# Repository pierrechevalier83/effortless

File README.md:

# WIP

This is not ready for any kind of public consumption.
It's just on GitHub as a backup for now.

It's the design of my next keyboard that is a work-in-progress.

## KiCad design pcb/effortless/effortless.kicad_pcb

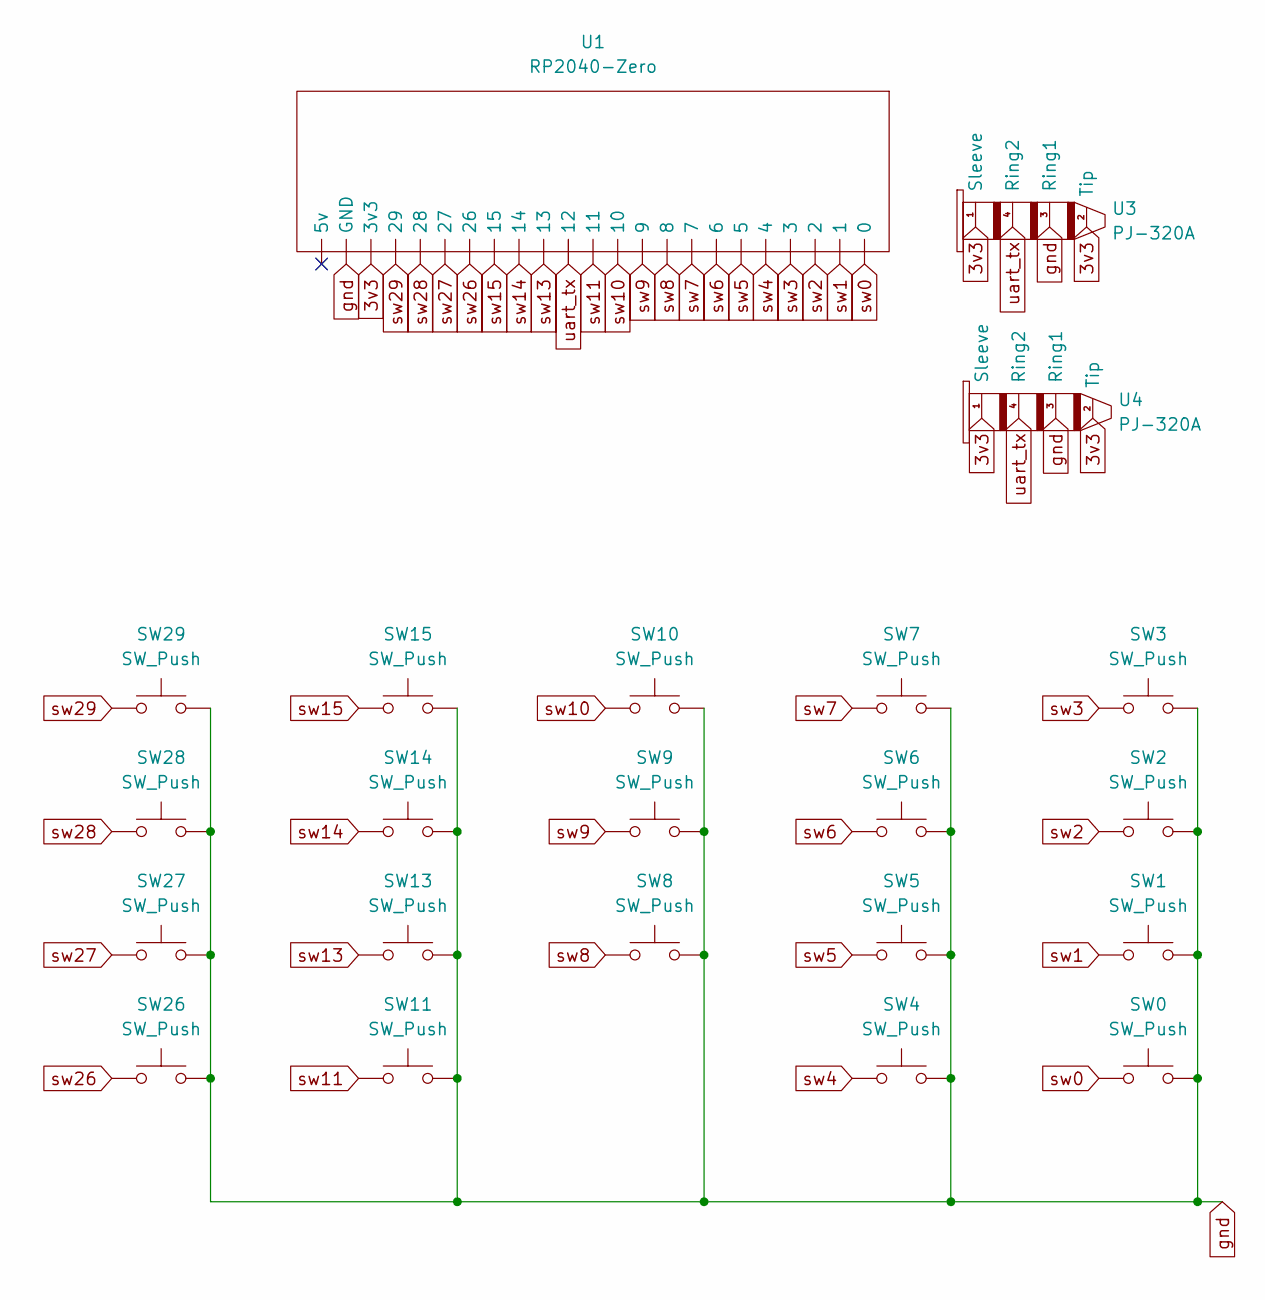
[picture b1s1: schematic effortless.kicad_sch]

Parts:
SW0, SW1, SW2, SW3, SW4, SW5, SW6, SW7, SW8, SW9, SW10, SW11, SW13, SW14, SW15, SW26, SW27, SW28, SW29: SW_Push; effortless_switch
U1: RP2040-Zero
U3, U4: PJ-320A

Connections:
3v3: U1.3v3, U3.1 (Sleeve), U3.2 (Tip), U4.1 (Sleeve), U4.2 (Tip)
gnd: SW0.2, SW1.2, SW2.2, SW3.2, SW4.2, SW5.2, SW6.2, SW7.2, SW8.2, SW9.2, SW10.2, SW11.2, SW13.2, SW14.2, SW15.2, SW26.2, SW27.2, SW28.2, SW29.2, U1.GND, U3.3 (Ring1), U4.3 (Ring1)
sw0: SW0.1, U1.0
sw1: SW1.1, U1.1
sw2: SW2.1, U1.2
sw3: SW3.1, U1.3
sw4: SW4.1, U1.4
sw5: SW5.1, U1.5
sw6: SW6.1, U1.6
sw7: SW7.1, U1.7
sw8: SW8.1, U1.8
sw9: SW9.1, U1.9
sw10: SW10.1, U1.10
sw11: SW11.1, U1.11
sw13: SW13.1, U1.13
sw14: SW14.1, U1.14
sw15: SW15.1, U1.15
sw26: SW26.1, U1.26
sw27: SW27.1, U1.27
sw28: SW28.1, U1.28
sw29: SW29.1, U1.29
uart_tx: U1.12, U3.4 (Ring2), U4.4 (Ring2)

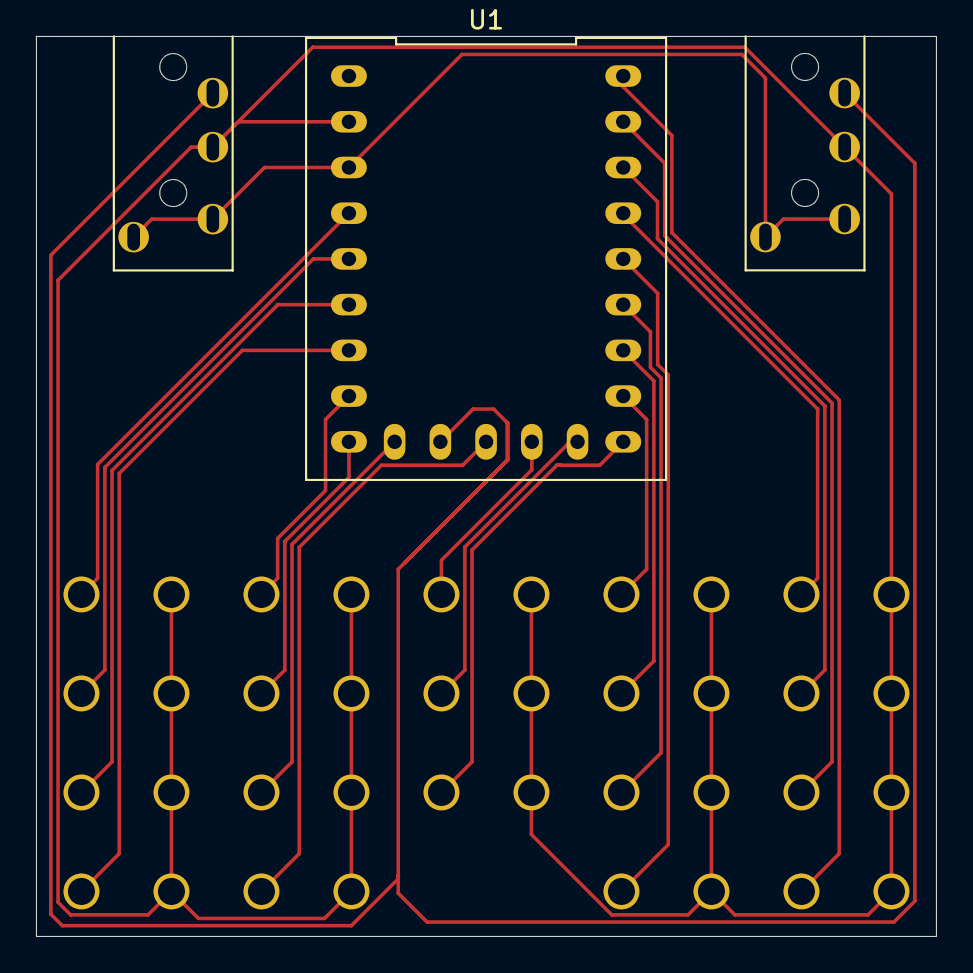
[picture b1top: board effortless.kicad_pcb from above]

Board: 2 copper layers, 50.0 x 50.0 mm, 22 parts (0 on the bottom side), 22 nets.

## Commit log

2024-12-01 Add opencascade-rs as a submodule
2024-12-01 Add gitignore
2024-12-01 Start writing the 3d model for the keyboard
    Early days.
    For now, we have
    * defined the geometry of a single switch
    * defined the geometry of the main switch matrix
    There are a number of TODOs:
    * hard-coded numbers as I'm tinkering
2024-12-01 Add a readme reflecting the current status of this project
2024-12-01 Add submodules for PCB
2024-12-01 Ignore PCB outputs
2024-12-02 Add PCB
2024-12-02 Remove scratchpad.rs
2024-12-05 Fix incorrect y spacing
2024-12-05 Rought sketch a pair of thumbs. It's not attached to the keyboard yet
2024-12-05 Add thumbs that do nothing yet. Simplify ProjectedXYSketch
2024-12-05 Clean-up right face, rigourously define y lofts
2024-12-05 Rename sketches consistently
2024-12-05 Rigorously define the x spacing
    Only cut if the column is above another to avoid weird artifact.
    Code is hacky for now, but principle is sound.
2024-12-05 Use margin in every direction to reduce the number of sketches necessary
2024-12-05 Unify the thumbs to the main body
    It now needs a couple extra cuts above the thumbs, but that allows for
    a flowing shape all around the body of the keyboard
2024-12-05 Refine the shape just a touch
2024-12-05 Streamline the shape some more
2024-12-05 Define cutout above the thumbs
2024-12-05 Make the thumbs cutout a bit prettyer
2024-12-06 Fix stickyness on column 2
2024-12-18 Cut-out the main pcb
2024-12-18 Cut-out the rp2040, offset electronics by 3mm
2024-12-18 Ignore lock files
2024-12-18 Cut-out the jack
2024-12-18 Give margin for PCB and jack so it can slide in at an angle
2024-12-21 Add cutouts to access jack and USB C
2024-12-21 Brute force the switch wire holes with straight lines
    It doesn't look good as bare wires would short each other, but it's a
    start.
    We'll need to think of nicer routing next.
2024-12-21 Hard-code a routing that just about works
    It's hairy and manually tuned, but it avoids wires intersecting each
    other and it connects every switch on the plate to their PCB holes.
2024-12-21 Wire the thumbs to reach functionally complete model
    The code could do with significant clean-up, and I'll have to print the
    model to ensure correctness in the physical world.
2024-12-24 Add space between the wires
2025-01-16 USB cutout: go off measurements rather than guesses
2025-01-16 Give more margin to the PCB and move it left so it still fits
2025-01-16 Rethink the wiring strategy with a cutout above the PCB holes
    This allows us much more freedom and avoids sharp bends inside the body
    that are preventing running the wires in practice.
2025-01-17 Make the wall thickness behind the PCB 2mm to improve jack fit
2025-01-17 Add supporting feature for right part of the RP2040 cutout
2025-01-17 Add extra clearance for wire exits
2025-01-17 Add extra clearance around PCB and jack cutouts
2025-01-17 Reduce PCB clearance in the Y dimension
2025-01-17 Implement right hand
    It is not strictly symmetrical, so can't just be mirrored.
    We need to mirror the switch footprint, so we can keep the same switch
    after mirroring the entire shape in the slicer.
    I would have mirrored the shape, but apparently opencascade doesn't
    make it easy.
    This produces a mirrored right hand. Remember to mirror it in the slicer
2025-01-17 Special case col 0 for the right hand
    It needs a deeper hole due to the stagger.
    Applying deeper holes for the entire keyboard like we did before is too
    much of a compromise.
    This is less elegant in terms of code, but it minimizes the differences
    between right and left hand and makes it more likely the wires can all
    have an easy path through their holes.
2025-01-18 Write firmware for the effortless
2025-03-02 Replace hardcoded Z0 with BASE_Z_OFFSET constant
2025-03-02 Refactor PCB offset into PCB_X_OFFSET constant
2025-03-02 Move PCB 2mm to the left by adjusting PCB_X_OFFSET
2025-03-02 Simplify geometry with symmetric switches and shared wire routing
    Largely simplify the keyboard overall in a few ways:
    * Switches are now symmetrical, which means that a mirrored version of
    the keyboard can be printed for each hand
    * Instead of wire holes under each pin, there is a deeper cutout under
    each switch which can accomodate wires from pins anywhere
    * Instead of one pipe per pin routing cables to the PCB area, we now
